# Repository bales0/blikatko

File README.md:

# blikatko
Bicycle back light with some features

Simple bicycle back light with mode switch, low voltage warning, deep sleep when OFF.
Use ATTINY45L, set internal 8MHz oscilator fuse, disable WDT and BROWN_OUT fuses. Compile with Arduino IDE.

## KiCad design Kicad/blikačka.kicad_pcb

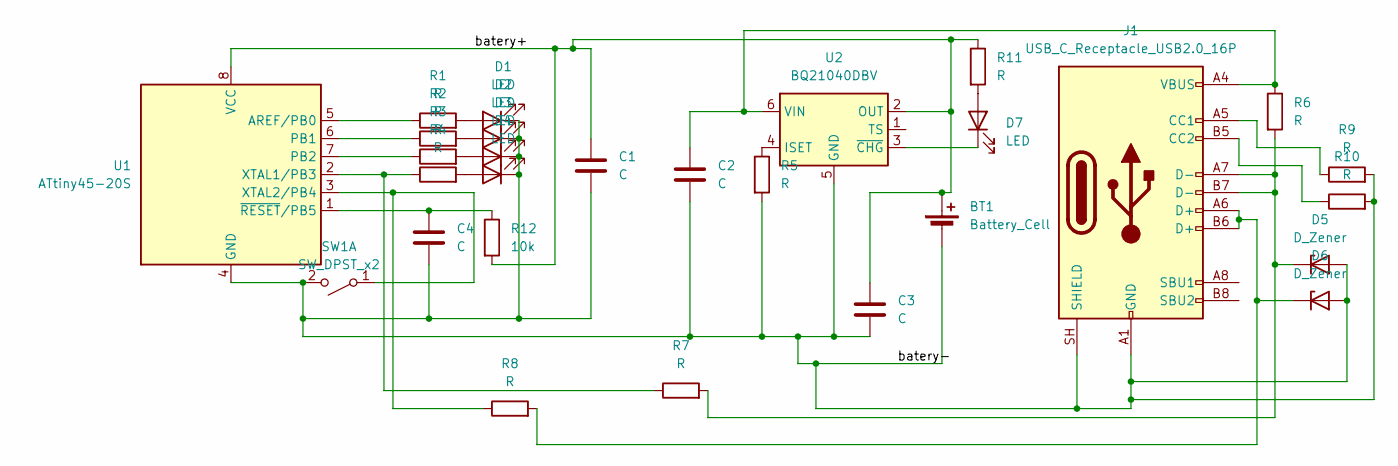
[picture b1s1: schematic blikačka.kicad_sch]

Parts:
BT1: Battery_Cell
C1, C2, C3: C; C_1206_3216Metric
C4: C; C_1206_3216Metric_Pad1.33x1.80mm_HandSolder
D1, D2, D3, D4: LED; LED-filament 33,5
D5, D6: D_Zener; D_1206_3216Metric
D7: LED; LED_1206_3216Metric_Pad1.42x1.75mm_HandSolder
J1: USB_C_Receptacle_USB2.0_16P; USB_C_Receptacle_Palconn_UTC16-G
R1, R2, R3, R4, R5, R6, R7, R8, R9, R10: R; R_1206_3216Metric
R11: R; R_1206_3216Metric_Pad1.30x1.75mm_HandSolder
R12: 10k; R_1206_3216Metric
SW1: SW_DPST_x2; SW_PUSH_6mm
U1: ATtiny45-20S; SOIC-8_5.3x5.3mm_P1.27mm
U2: BQ21040DBV; SOT-23-6

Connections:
/batery+: BT1.1 (+), C1.1, C3.1, R11.1, R12.2, U1.8 (VCC), U2.2 (OUT)
/batery-: BT1.2 (-), C1.2, C2.2, C3.2, C4.2, D1.1 (K), D2.1 (K), D3.1 (K), D4.1 (K), D5.2 (A), D6.2 (A), J1.A1 (GND), J1.A12 (GND), J1.B1 (GND), J1.B12 (GND), J1.SH (SHIELD), R5.2, R9.2, R10.2, SW1.2 (B), U1.4 (GND), U2.5 (GND)
unnamed: D1.2 (A), R1.2
unnamed: D2.2 (A), R2.2
unnamed: D3.2 (A), R3.2
unnamed: D4.2 (A), R4.2
unnamed: D5.1 (K), J1.A7 (D-), J1.B7 (D-), R6.2, R7.2
unnamed: D6.1 (K), J1.A6 (D+), J1.B6 (D+), R8.2
unnamed: D7.2 (A), R11.2
unnamed: D7.1 (K), U2.3 (~CHG)
unnamed: J1.A5 (CC1), R9.1
unnamed: J1.B5 (CC2), R10.1
unnamed: R8.1, SW1.1 (A), U1.3 (XTAL2/PB4)
unnamed: R1.1, U1.5 (AREF/PB0)
unnamed: R2.1, U1.6 (PB1)
unnamed: R3.1, U1.7 (PB2)
unnamed: R4.1, R7.1, U1.2 (XTAL1/PB3)
unnamed: C4.1, R12.1, U1.1 (~RESET/PB5)
unnamed: R5.1, U2.4 (ISET)
unnamed: C2.1, J1.A4 (VBUS), J1.A9 (VBUS), J1.B4 (VBUS), J1.B9 (VBUS), R6.1, U2.6 (VIN)

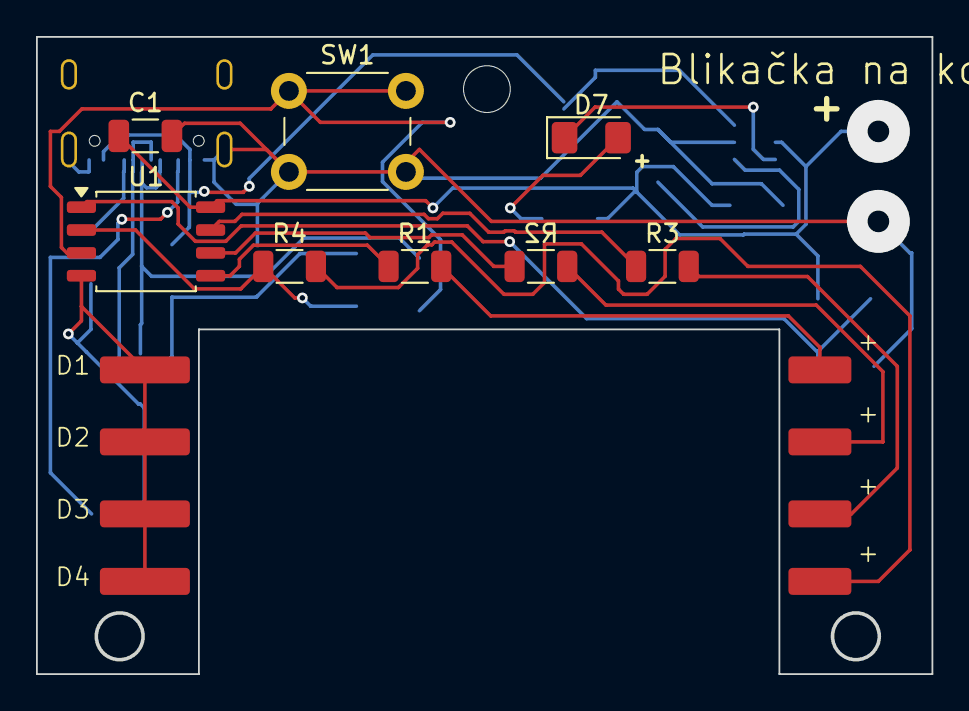
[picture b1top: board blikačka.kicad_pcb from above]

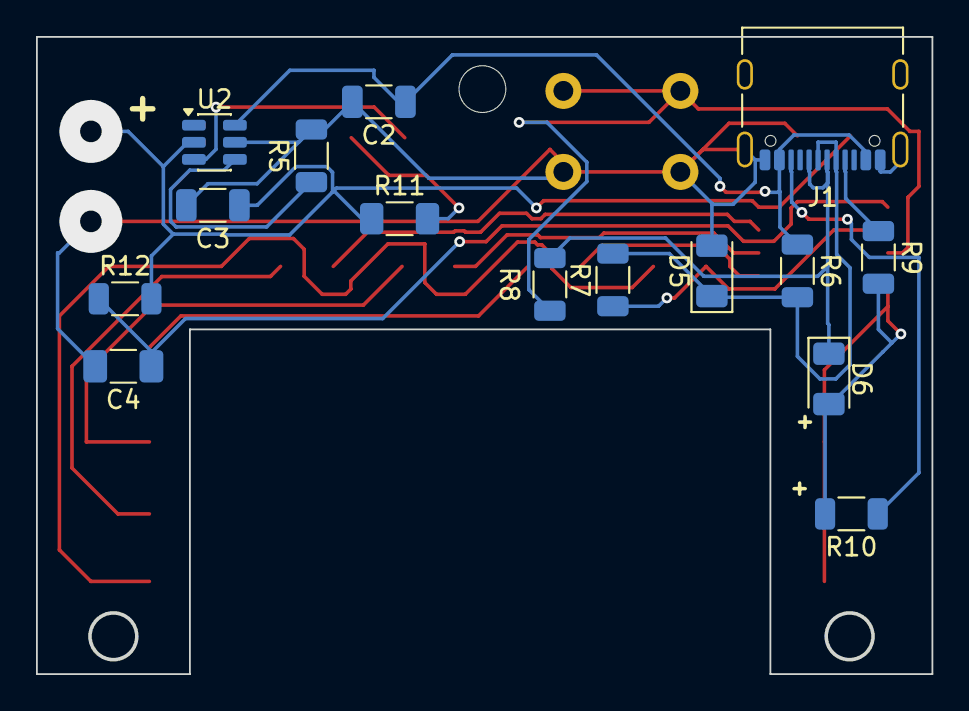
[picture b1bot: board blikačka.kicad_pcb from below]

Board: 2 copper layers, 49.7 x 35.3 mm, 27 parts (15 on the bottom side), 20 nets.

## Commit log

2026-06-01 added sleep function, low voltage warning
2026-06-01 Enhance README with product description
    Added a brief description of the bicycle back light features.
2026-06-01 Fix fuse name and add compilation instructions
    Corrected the fuse name from 'BRON_OUT' to 'BROWN_OUT' and added compilation details.
2026-06-01 Update README with ATTINY45L fuse settings
2026-06-01 finetune sleep and low voltage indication
2026-06-01 added Kicad files
2026-06-09 license
